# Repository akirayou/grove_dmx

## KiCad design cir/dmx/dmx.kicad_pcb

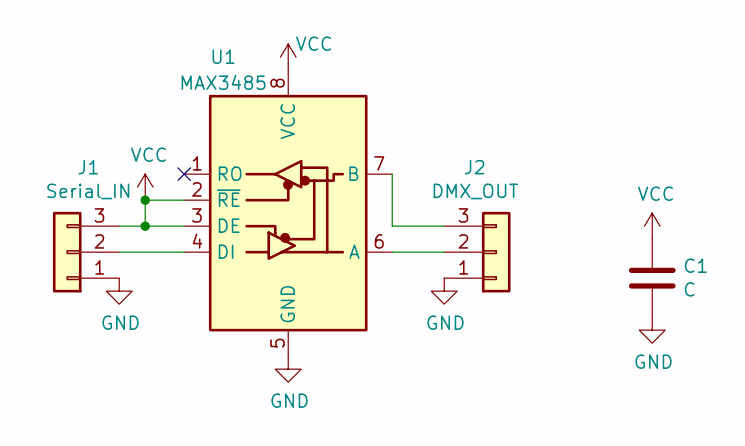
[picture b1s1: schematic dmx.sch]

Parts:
C1: C; C_0603_1608Metric_Pad1.08x0.95mm_HandSolder
J1: Serial_IN; PinHeader_1x03_P2.00mm_Horizontal
J2: DMX_OUT; PinHeader_1x03_P2.00mm_Horizontal
U1: MAX3485; SOP-8_3.9x4.9mm_P1.27mm

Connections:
GND: C1.2, J1.1, J2.1, U1.5 (GND)
unnamed: J1.2, U1.4 (DI)
unnamed: J2.2, U1.6 (A)
unnamed: J2.3, U1.7 (B)
VCC: C1.1, J1.3, U1.2 (~RE), U1.3 (DE), U1.8 (VCC)

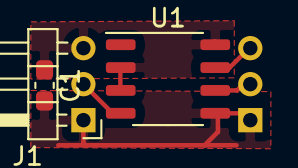
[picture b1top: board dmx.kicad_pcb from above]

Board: 2 copper layers, 4 parts (1 on the bottom side), 5 nets.
